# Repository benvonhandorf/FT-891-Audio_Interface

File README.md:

# FT-891-Audio_Interface
Yaesu FT-891 to headset audio interface

A small project to allow easy interface of a Yaesu FT-891 to a cellphone headset or an Aviation headset.

[Derived from the work described here](https://docsbydesign.com/2015/10/31/aircraft-headset-to-ham-radio-adapter/) by Bob Watson.

Possible additional filtering on the input and output paths inspired by [W2AEW's D-104 microphone preamp](https://www.qsl.net/w2aew/myd104amp.html) and possible additional work based on [KR6ZY's station audio interface](https://github.com/SmittyHalibut/station-console).

Relies upon my [various KiCAD libraries](https://github.com/benvonhandorf/kicad-library).

73 de AB4EN - Ben

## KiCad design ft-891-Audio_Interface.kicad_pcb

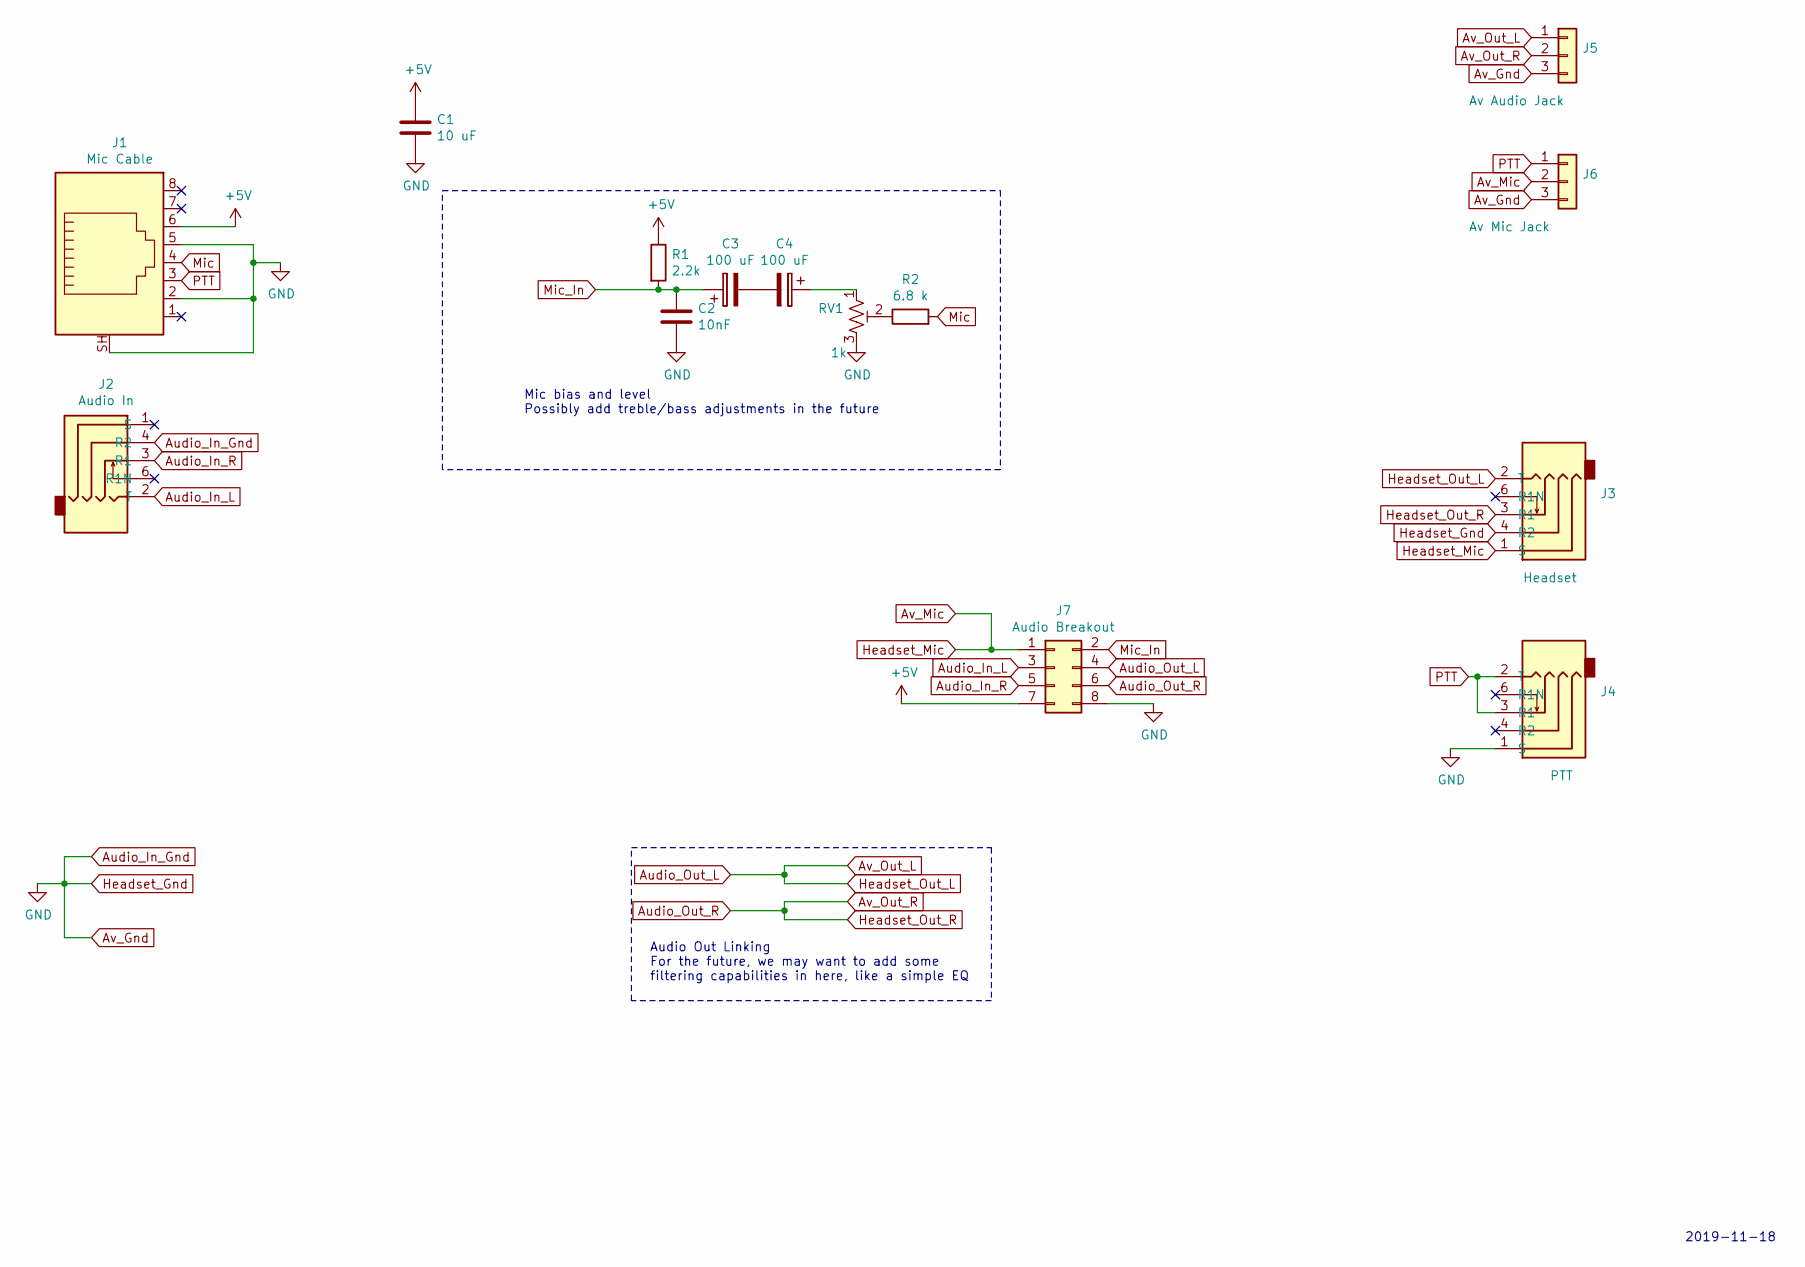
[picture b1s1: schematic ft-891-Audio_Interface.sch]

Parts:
C1: 10 uF; C_1206_HandSoldering
C2: 10nF; C_1206_HandSoldering
C3, C4: 100 uF; CP_Elec_8x10
J1: Mic Cable; Molex_0855055002_RJ-45_Jack_Shielded_Yaesu_Numbering
J2: Audio In; SJ-43515RS-SMT-TR
J3: Headset; SJ-43515RS-SMT-TR
J4: PTT; SJ-43515RS-SMT-TR
J5: Av Audio Jack; Pin_Header_Straight_1x03_Pitch2.54mm
J6: Av Mic Jack; Pin_Header_Straight_1x03_Pitch2.54mm
J7: Audio Breakout; Pin_Header_Straight_2x04_Pitch2.54mm
R1: 2.2k; R_1206_HandSoldering
R2: 6.8 k; R_1206_HandSoldering
RV1: 1k; Potentiometer_Trimmer_ACP_CA6v_Horizontal

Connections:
+5V: C1.1, J1.6, J7.7, R1.1
Audio_In_Gnd: C1.2, C2.2, J1.2, J1.5, J1.SH, J2.4 (R2), J3.4 (R2), J4.1 (S), J5.3, J6.3, J7.8, RV1.3
Audio_In_L: J2.2 (T), J7.3
Audio_In_R: J2.3 (R1), J7.5
Audio_Out_L: J3.2 (T), J5.1, J7.4
Audio_Out_R: J3.3 (R1), J5.2, J7.6
Av_Mic: J3.1 (S), J6.2, J7.1
Mic: J1.4, R2.2
Mic_In: C2.1, C3.1, J7.2, R1.2
unnamed: C3.2, C4.2
unnamed: C4.1, RV1.1
unnamed: R2.1, RV1.2
PTT: J1.3, J4.2 (T), J4.3 (R1), J6.1

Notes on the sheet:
Audio Out Linking For the future, we may want to add some filtering capabilities in here, like a simple EQ
Mic bias and level Possibly add treble/bass adjustments in the future
2019-11-18

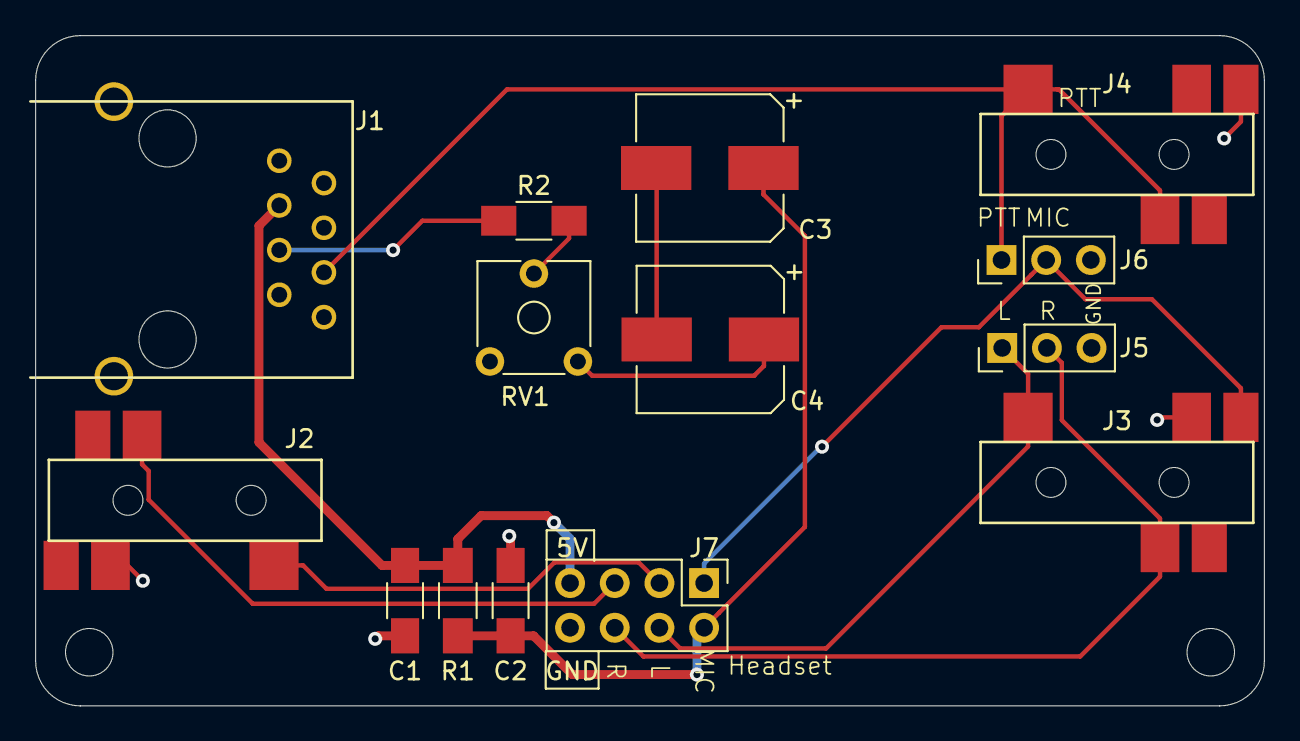
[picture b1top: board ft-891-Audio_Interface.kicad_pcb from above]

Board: 2 copper layers, 69.9 x 38.1 mm, 14 parts (0 on the bottom side), 13 nets.

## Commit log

2019-11-29 Basic schematic without filtering
2019-11-29 First pass at routing and layout
2019-12-01 Add expansion header and NPTH for mounting
2020-05-17 FT-891 interface v2 - Fix earlier mistakes, larger board, mounting holes
2022-07-02 Backup
